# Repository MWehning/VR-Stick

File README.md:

# VR-Stick
reimagining of the VR-Shield using the nRF24LE1 microcontroller and radio chip

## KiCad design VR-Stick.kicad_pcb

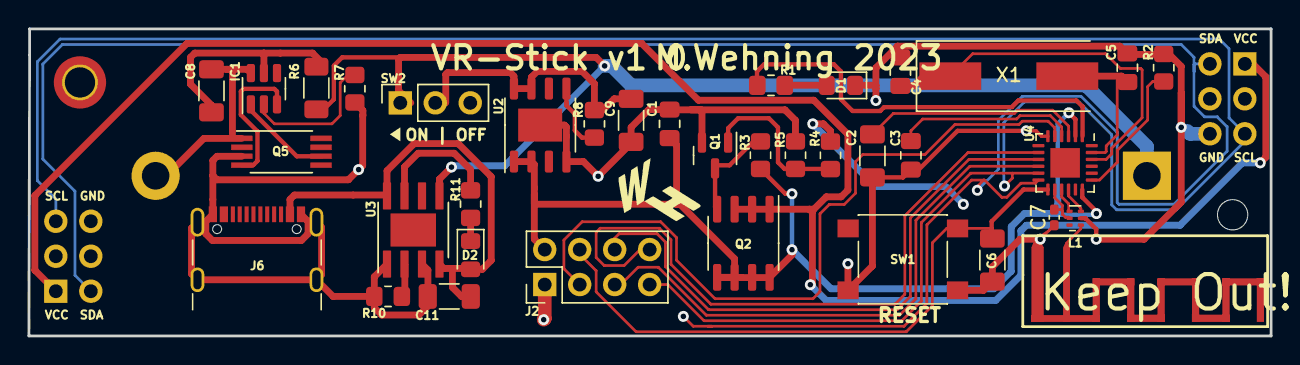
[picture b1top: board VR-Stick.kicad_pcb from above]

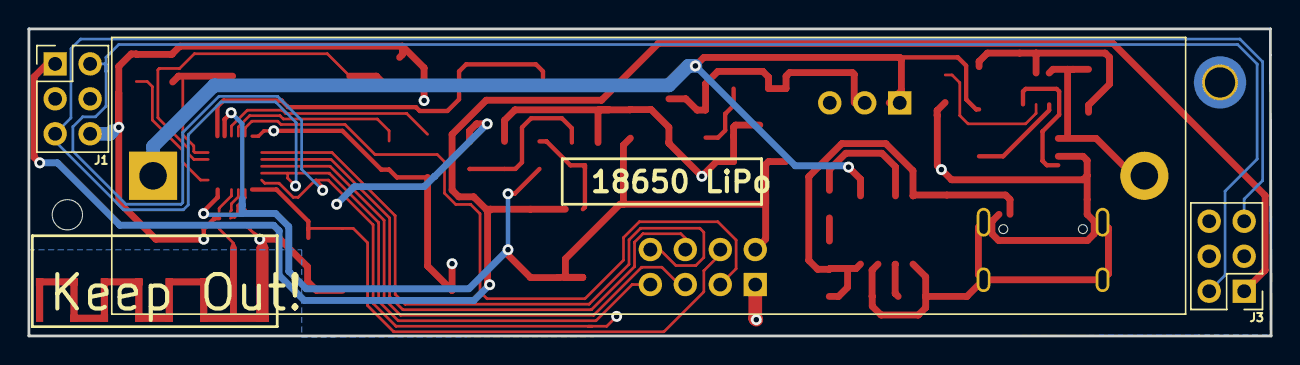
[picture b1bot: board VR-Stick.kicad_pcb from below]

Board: 2 copper layers, 90.2 x 22.3 mm, 38 parts (3 on the bottom side), 34 nets.

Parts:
C1: 100nF; C_0805_2012Metric_Pad1.18x1.45mm_HandSolder
C2, C6, C8, C9, C11: 100nF; C_1206_3216Metric_Pad1.33x1.80mm_HandSolder
C3: 33nF; C_0805_2012Metric_Pad1.18x1.45mm_HandSolder
C4, C5: 15pF; C_0805_2012Metric_Pad1.18x1.45mm_HandSolder
C7: 2.2nF; C_0402_1005Metric_Pad0.74x0.62mm_HandSolder
D1: BLUE; LED_0805_2012Metric_Pad1.15x1.40mm_HandSolder
D2: RED; LED_0805_2012Metric_Pad1.15x1.40mm_HandSolder
IC1: DW01A; SOT-23-6
J1, J3: I2C Port; PinHeader_2x03_P2.54mm_Vertical
J2: Conn_02x04_Odd_Even; PinHeader_2x04_P2.54mm_Vertical
J4: Conn_01x02_Pin; BatteryHolder_MPD_BH-18650-PC2
J6: USB_C_Receptacle_PowerOnly_6P; USB_C_Receptacle_GCT_USB4105-xx-A_16P_TopMnt_Horizontal
L1: Balun_Johanson_1.6x0.8mm
Q1: BC847; SOT-23
Q2: IRF7404; SOIC-8_3.9x4.9mm_P1.27mm
Q5: FS8205A; SOP65P640X120-8N
R1, R11: 180; R_0805_2012Metric_Pad1.20x1.40mm_HandSolder
R2: 22k 1%; R_0805_2012Metric_Pad1.20x1.40mm_HandSolder
R3: 33k; R_0805_2012Metric_Pad1.20x1.40mm_HandSolder
R4: 3.3k; R_0805_2012Metric_Pad1.20x1.40mm_HandSolder
R5: 100k; R_0805_2012Metric_Pad1.20x1.40mm_HandSolder
R6: 100; R_1206_3216Metric_Pad1.30x1.75mm_HandSolder
R7: 1k; R_0805_2012Metric_Pad1.20x1.40mm_HandSolder
R8: 10k; R_0805_2012Metric_Pad1.20x1.40mm_HandSolder
R10: R_PROG; R_0805_2012Metric_Pad1.20x1.40mm_HandSolder
SW1: RESET; SW_Push_1P1T_NO_6x6mm_H9.5mm
SW2: POWER; PinSocket_1x03_P2.54mm_Vertical
U2: XC6220B331QR-G; HTSOP-8-1EP_3.9x4.9mm_P1.27mm_EP2.4x3.2mm
U3: TP4056; SOP127P600X175-9N
U4: QFN-24-1EP_4x4mm_P0.5mm_EP2.15x2.15mm
X1: 16MHz; Crystal_SMD_HC49-SD

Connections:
+3V3: C1.2, J2.2, Q2.5 (D), Q2.6 (D), Q2.7 (D), Q2.8 (D), R3.1, U2.1 (VOUT), U2.2 (VOUT), U4.2 (VDD), U4.7 (VDD), U4.18 (VDD), U4.21 (VDD)
-BATT: C8.1, IC1.6 (VSS), J4.2, Q5.1
/ANT1: L1.4 (BAL2), U4.15 (ANT1)
/ANT2: L1.3 (BAL1), U4.16 (ANT2)
/B+: J4.1, R6.1, SW2.1, U3.5 (BAT)
/CSN: J2.5, U4.10 (P0.4)
/LED: R1.1, U4.1 (P0.1)
/MISO: J1.5, J2.7, J3.5, U4.11 (P0.5)
/MOSI: J2.6, U4.9 (P0.3)
/PROG: J2.3, U4.5 (PROG)
/RST: C6.1, J2.4, SW1.1, U4.13 (~RESET)
/SCK: J2.8, U4.8 (P0.2)
/SD0: J1.2, J3.2, U4.12 (P0.6)
/VUSB: C11.1, D2.2 (A), J6.A9 (VBUS), J6.B9 (VBUS), U3.4 (VCC), U3.8 (CE)
/V_PA: C7.2, L1.5 (DC), U4.14 (VDD_PA)
GND: C1.1, C2.1, C3.1, C4.2, C5.1, C6.2, C7.1, C9.1, C11.2, D1.1 (K), J1.6, J2.1, J3.6, J6.A12 (GND), J6.B12 (GND), J6.S1 (SHIELD), L1.2 (GND), Q1.2 (E), Q5.3, R2.1, R5.1, R7.2, R10.2, SW1.2, U2.4 (GND), U2.9 (Thermal), U3.1 (TEMP), U3.3 (GND), U4.6 (VSS)
unnamed: C9.2, R8.1, SW2.2, U2.7 (VIN), U2.8 (VIN)
unnamed: D1.2 (A), R1.2
unnamed: D2.1 (K), R11.1
unnamed: IC1.2 (CS), R7.1
unnamed: IC1.3 (OC), Q5.4
unnamed: IC1.1 (OD), Q5.6
unnamed: C8.2, IC1.5 (VDD), R6.2
unnamed: Q1.1 (B), R4.2, R5.2
unnamed: Q1.3 (C), Q2.4 (G), R3.2
unnamed: R8.2, U2.5 (CE)
unnamed: R10.1, U3.2 (PROG)
unnamed: R11.2, U3.7 (~CHRG)
unnamed: C2.2, U4.3 (DEC1)
unnamed: C3.2, U4.4 (DEC2)
unnamed: R2.2, U4.19 (IREF)
unnamed: C5.2, U4.23 (XC1), X1.2
unnamed: C4.1, U4.22 (XC2), X1.1
VBUS: J1.1, J3.1, Q2.1 (S), Q2.2 (S), Q2.3 (S)

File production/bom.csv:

Designator,Footprint,Quantity,Value,LCSC Part #
C1,0805,1,100nF,
"C11, C2, C6, C8, C9",1206,5,100nF,
C3,0805,1,33nF,
"C4, C5",0805,2,15pF,
C7,0402,1,2.2nF,
D1,0805,1,BLUE,
D2,0805,1,RED,
IC1,SOT-23-6,1,DW01A,
"J1, J3",PinHeader_2x03_P2.54mm_Vertical,2,I2C Port,
J2,PinHeader_2x04_P2.54mm_Vertical,1,Conn_02x04_Odd_Even,
J4,BatteryHolder_MPD_BH-18650-PC2,1,Conn_01x02_Pin,
J6,USB_C_Receptacle_GCT_USB4105-xx-A_16P_TopMnt_Horizontal,1,USB_C_Receptacle_PowerOnly_6P,
L1,Balun_Johanson_1.6x0.8mm,1,~,
Q1,SOT-23,1,BC847,
Q2,SOIC-8_3.9x4.9mm_P1.27mm,1,IRF7404,
Q5,SOP65P640X120-8N,1,FS8205A,
"R1, R11",0805,2,180,
R10,0805,1,R_PROG,
R2,0805,1,22k 1%,
R3,0805,1,33k,
R4,0805,1,3.3k,
R5,0805,1,100k,
R6,1206,1,100,
R7,0805,1,1k,
R8,0805,1,10k,
SW1,SW_Push_1P1T_NO_6x6mm_H9.5mm,1,RESET,
SW2,PinSocket_1x03_P2.54mm_Vertical,1,POWER,
U2,HTSOP-8-1EP_3.9x4.9mm_P1.27mm_EP2.4x3.2mm,1,XC6220B331QR-G,
U3,SOP127P600X175-9N,1,TP4056,
U4,QFN-24-1EP_4x4mm_P0.5mm_EP2.15x2.15mm,1,~,
X1,Crystal_SMD_HC49-SD,1,16MHz,
